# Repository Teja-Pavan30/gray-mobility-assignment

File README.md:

# gray-mobility-assignment
led glow

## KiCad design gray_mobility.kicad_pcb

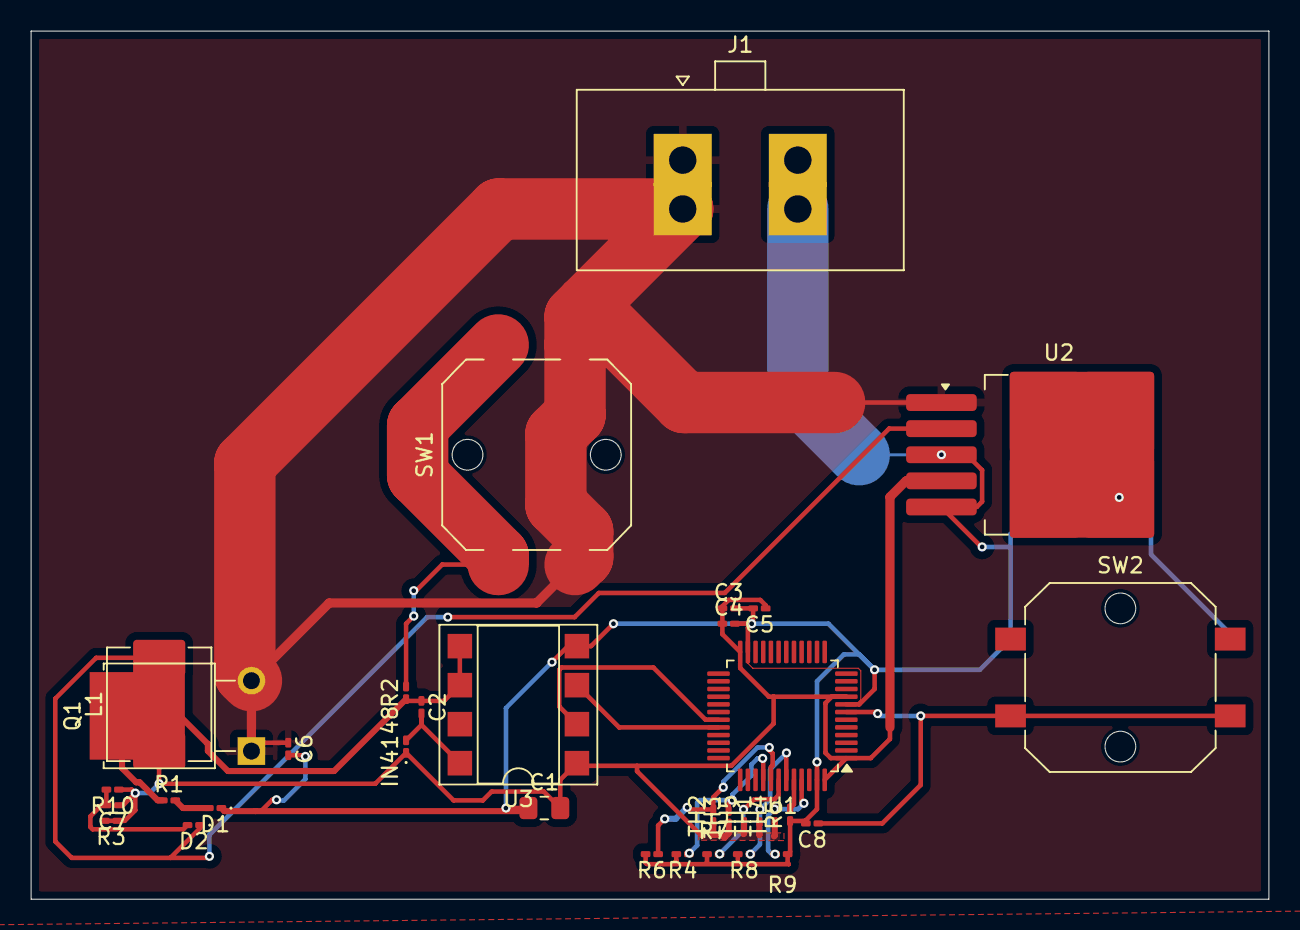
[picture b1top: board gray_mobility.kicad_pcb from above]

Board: 2 copper layers, 80.6 x 56.5 mm, 34 parts (0 on the bottom side), 17 nets.

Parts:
C1: 10uF; C_0805_2012Metric_Pad1.18x1.45mm_HandSolder
C2: 2.2uF; C_0201_0603Metric_Pad0.64x0.40mm_HandSolder
C3, C4: 100nF; C_0201_0603Metric_Pad0.64x0.40mm_HandSolder
C5: 1uF; C_0201_0603Metric_Pad0.64x0.40mm_HandSolder
C6: 680uF; C_0201_0603Metric_Pad0.64x0.40mm_HandSolder
C7: 220uF; C_0201_0603Metric_Pad0.64x0.40mm_HandSolder
C8: 0.1uF; C_0201_0603Metric_Pad0.64x0.40mm_HandSolder
D1: LED; LED_0201_0603Metric_Pad0.64x0.40mm_HandSolder
D2: D; D_0201_0603Metric_Pad0.64x0.40mm_HandSolder
IN4148: D; D_0201_0603Metric_Pad0.64x0.40mm_HandSolder
J1: Conn_01x02_Pin; Molex_Sabre_43160-0102_1x02_P7.49mm_Vertical
L1: 30uH; L_Abracon_ASPI-0630LR
Q1: IRFB4110; TO-251-2-1EP_Horizontal_TabDown
R1: 0; R_0201_0603Metric_Pad0.64x0.40mm_HandSolder
R2: 150; R_0201_0603Metric_Pad0.64x0.40mm_HandSolder
R3: 1k; R_0201_0603Metric_Pad0.64x0.40mm_HandSolder
R4, R6, R7, R8, R9: 10k; R_0201_0603Metric_Pad0.64x0.40mm_HandSolder
R5: 10kR; R_0201_0603Metric_Pad0.64x0.40mm_HandSolder
R10: 2k; R_0201_0603Metric_Pad0.64x0.40mm_HandSolder
SW1, SW2: SW_Push; SW_Push_1P1T_NO_CK_PTS125Sx43PSMTR
TH1, TH2, TH3, TH4, TH5: Thermistor_NTC; R_0201_0603Metric_Pad0.64x0.40mm_HandSolder
U1: STM32F030C8Tx; LQFP-48_7x7mm_P0.5mm
U2: LM2596S-3.3; TO-263-5_TabPin3
U3: IR2101; DIP-8_W7.62mm_SMDSocket_SmallPads

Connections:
+40V: C6.1, J1.1, Q1.1 (D), Q1.2 (G), SW1.2, U2.1 (VIN)
/HIN: U1.31 (PA10), U3.2 (HIN)
/LIN: U1.32 (PA11), U3.3 (LIN)
/NRST: C8.1, SW2.2, U1.7 (NRST)
/OUT: C1.2, C3.1, C4.1, C5.1, C7.1, IN4148.1 (K), L1.1, R3.1, R3.2, R10.1, TH1.1, TH2.1, TH3.1, TH4.1, TH5.1, U1.1 (VDD), U1.9 (VDDA), U1.24 (VDD), U1.48 (VDD), U2.4 (FB), U3.1 (VCC)
/PB4: R4.1, TH3.2, U1.40 (PB4)
/PB5: R6.1, TH2.2, U1.41 (PB5)
/PB6: R7.1, TH5.2, U1.42 (PB6)
/PB7: R8.1, TH1.2, U1.43 (PB7)
/PB8: R9.1, TH4.2, U1.45 (PB8)
GND: C1.1, C3.2, C4.2, C5.2, C6.2, C7.2, C8.2, D1.1 (K), D2.2 (A), J1.2, R4.2, R5.1, R6.2, R7.2, R8.2, R9.2, R10.2, SW2.1, U1.8 (VSSA), U1.23 (VSS), U1.47 (VSS), U2.3 (GND), U2.5 (~ON/OFF), U3.4 (COM)
unnamed: D1.2 (A), R1.2
unnamed: D2.1 (K), L1.2, U2.2 (OUT)
unnamed: C2.2, IN4148.2 (A), U3.8 (VB)
unnamed: C2.1, Q1.3 (S), R1.1, R2.1, U3.5 (LO), U3.6 (VS)
unnamed: R2.2, SW1.1
unnamed: R5.2, U1.44 (BOOT0)
